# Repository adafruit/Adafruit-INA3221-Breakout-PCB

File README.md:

## Adafruit INA3221 - Triple 0-26 VDC, ±3.2 Amp Power Monitor - STEMMA QT / Qwiic PCB

<a href="http://www.adafruit.com/products/6062"><br/>
Click here to purchase one from the Adafruit shop</a>

PCB files for the Adafruit INA3221 - Triple 0-26 VDC, ±3.2 Amp Power Monitor - STEMMA QT / Qwiic. 

Format is EagleCAD schematic and board layout
* https://www.adafruit.com/product/6062

### Description

This breakout board will solve all your multi-rail power-monitoring problems. Instead of struggling with up to 6 multimeters, you can just use the handy INA3221 chip on this breakout to both measure both the high side voltage and DC current draw of up to three power supplies over I2C with ±1% precision.

Most current-measuring devices such as our current panel meter are only good for low side measuring. That means that unless you want to get a battery involved, you have to stick the measurement resistor between the target ground and true ground. This can cause problems with circuits since electronics tend to not like it when the ground references change and move with varying current draw. This chip is much smarter - it can handle high or low side current measuring, up to +26VDC, even though it is powered with 3 or 5V. It will also report back that high side voltage, which is great for tracking battery life or solar panels.

A precision amplifier measures the voltage across the built-in 0.05 ohm, 1% sense resistors. Since the amplifier maximum input difference is ±163.8mV this means it can measure up to ±3.2 Amps. With the internal 13 bit ADC, the resolution at ±3.2A range is 0.4mA. Advanced hackers can remove the 0.05 ohm current sense resistor and replace it with their own to change the range (say a 0.01 ohm to measure up 16.4 Amps with a resolution of 2mA)

Usage is simple. Power the sensor itself with 3 to 5VDC and connect the two I2C pins up to your microcontroller - the logic level will be the same as the Vin power level. Then connect your target power supplies to VIN1/2/3+ and the loads to ground to VIN1/2/3-. If you want, set up over-current alerts on the warning or critical IRQ pins. We have libraries in both Arduino and CircuitPython/Python so you can use it with boards as simple as Arduino-compatible ATmegas all the way up to the latest Raspberry Pi's.

You don't even need to solder the I2C and power lines: we pre-attach 3.5mm terminal blocks and added SparkFun qwiic compatible STEMMA QT connectors for the I2C bus. Just wire up to your favorite micro using a STEMMA QT adapter cable. The Stemma QT connectors also mean the INA3221 can be used with our various associated accessories. QT Cable is not included, but we have a variety in the shop. If you need access to all of the pins, we include 0.1" pin header (so you can easily attach this sensor to a breadboard).

### License

Adafruit invests time and resources providing this open source design, please support Adafruit and open-source hardware by purchasing products from [Adafruit](https://www.adafruit.com)!

Designed by Limor Fried/Ladyada for Adafruit Industries.

Creative Commons Attribution/Share-Alike, all text above must be included in any redistribution. 
See license.txt for additional details.

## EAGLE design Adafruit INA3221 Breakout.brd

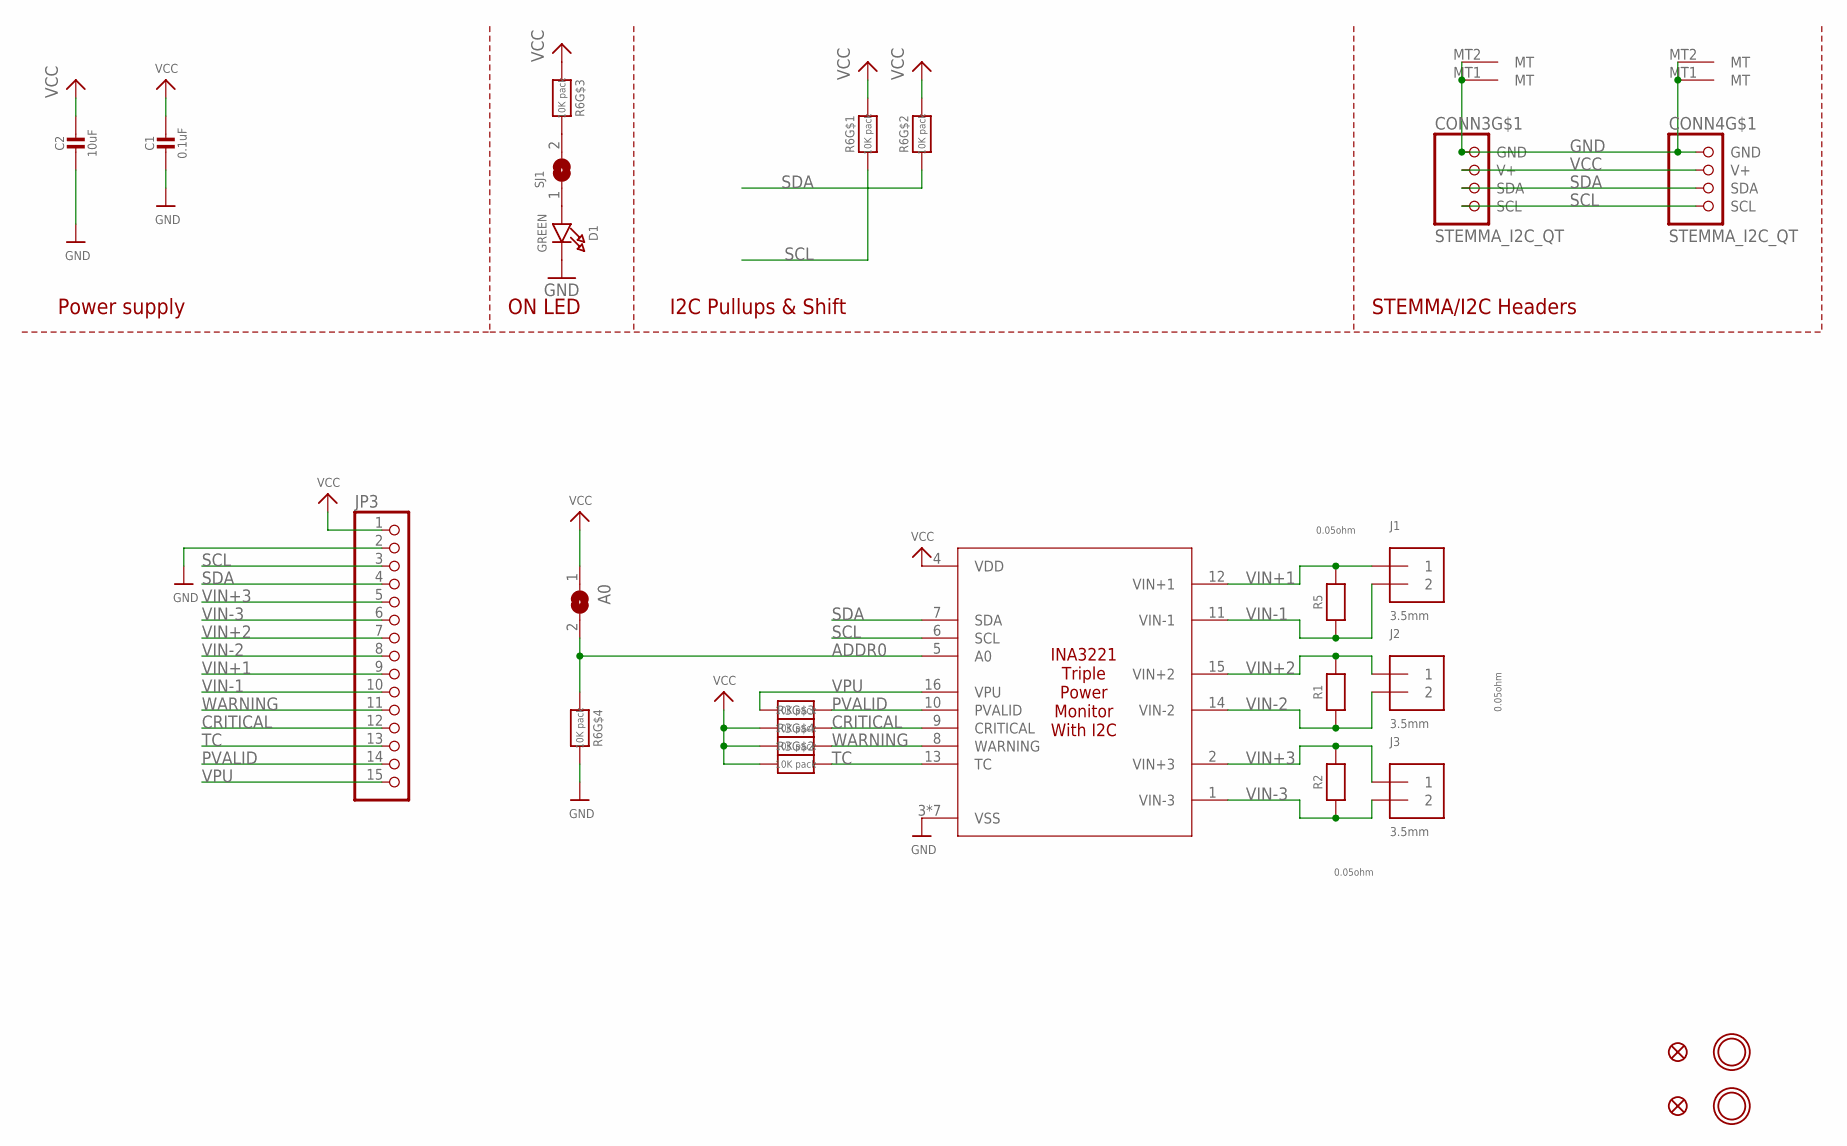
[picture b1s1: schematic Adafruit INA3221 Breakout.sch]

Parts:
A0: SOLDERJUMPERREFLOW_NOPASTE; SOLDERJUMPER_REFLOW_NOPASTE
C1: 0.1uF; 0603-NO
C2: 10uF; 0805-NO
CONN3, CONN4: STEMMA_I2C_QT; JST_SH4
D1: GREEN; CHIPLED_0603_NOOUTLINE
FID3, FID4: FIDUCIAL_1MM
IC1: INA3221; PVQFN-16
J1, J2, J3: 3.5mm; TERMBLOCK_1X2-3.5MM
JP3: HEADER-1X15; 1X15_ROUND_70
R1, R2, R5: 0.05ohm; _1206
R3, R6: 10K pack; RESPACK_4X0603
SJ1: SOLDERJUMPERCLOSED; SOLDERJUMPER_CLOSEDWIRE
U$20, U$21: MOUNTINGHOLE2.5; MOUNTINGHOLE_2.5_PLATED

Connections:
ADDR0: A0.2, IC1.5 (A0), R6.4 (1)
CRITICAL: IC1.9 (CRITICAL), JP3.12, R3.6 (2)
GND: C1.2, C2.2, CONN3.1 (GND), CONN3.MT1 (MT), CONN3.MT2 (MT), CONN4.1 (GND), CONN4.MT1 (MT), CONN4.MT2 (MT), D1.C, IC1.3 (VSS), IC1.P$18 (VSS), IC1.P$19 (VSS), IC1.P$20 (VSS), IC1.P$21 (VSS), IC1.P$22 (VSS), IC1.THERMAL (VSS), JP3.2, R6.5 (2)
unnamed: R6.6 (2), SJ1.2
unnamed: D1.A, SJ1.1
PVALID: IC1.10 (PVALID), JP3.14, R3.8 (2)
SCL: CONN3.4 (SCL), CONN4.4 (SCL), IC1.6 (SCL), JP3.3, R6.1
SDA: CONN3.3 (SDA), CONN4.3 (SDA), IC1.7 (SDA), JP3.4, R6.2 (1)
TC: IC1.13 (TC), JP3.13, R3.7 (2)
VCC: A0.1, C1.1, C2.1, CONN3.2 (V+), CONN4.2 (V+), IC1.4 (VDD), JP3.1, R3.2 (1), R3.3 (1), R3.4 (1), R6.3 (1), R6.7 (2), R6.8 (2)
VIN+1: IC1.12 (VIN+1), J1.1, JP3.9, R5.2
VIN+2: IC1.15 (VIN+2), J2.1, JP3.7, R1.2
VIN+3: IC1.2 (VIN+3), J3.1, JP3.5, R2.2
VIN-1: IC1.11 (VIN-1), J1.2, JP3.10, R5.1
VIN-2: IC1.14 (VIN-2), J2.2, JP3.8, R1.1
VIN-3: IC1.1 (VIN-3), J3.2, JP3.6, R2.1
VPU: IC1.16 (VPU), JP3.15, R3.1
WARNING: IC1.8 (WARNING), JP3.11, R3.5 (2)

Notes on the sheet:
I2C Pullups & Shift
STEMMA/I2C Headers
ON LED
Power supply

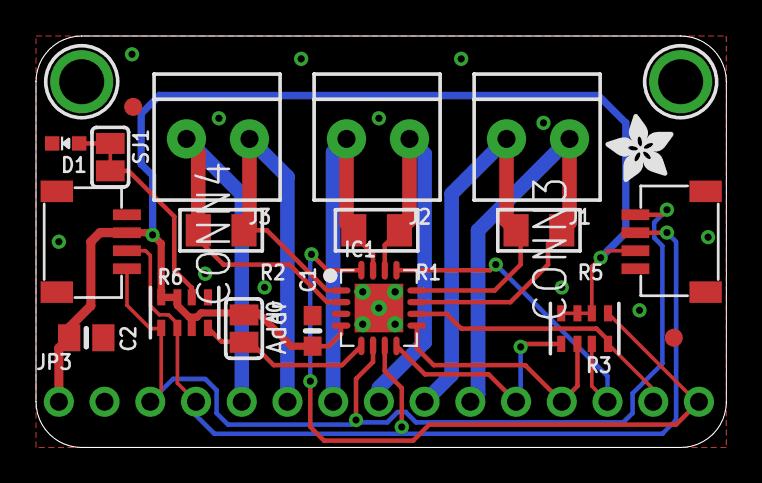
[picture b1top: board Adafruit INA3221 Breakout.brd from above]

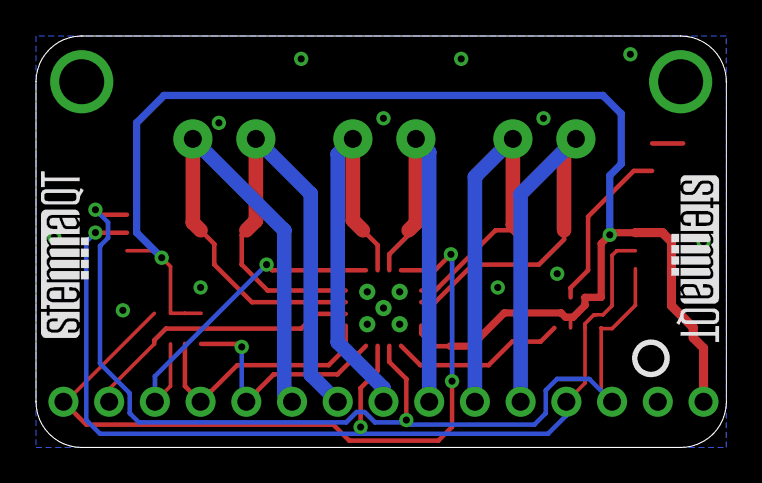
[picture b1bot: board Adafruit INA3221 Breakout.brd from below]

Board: 2 copper layers, 38.4 x 22.9 mm, 54 parts (7 on the bottom side), 18 nets.

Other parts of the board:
PLABEL0: PLABEL0
PLABEL1: PLABEL1
PLABEL2: PLABEL2
PLABEL3: PLABEL3
PLABEL4: PLABEL4
PLABEL5: PLABEL5
PLABEL6: PLABEL6
PLABEL7: PLABEL7
PLABEL8: PLABEL8
PLABEL9: PLABEL9
PLABEL10: PLABEL10
PLABEL11: PLABEL11
PLABEL12: PLABEL12
PLABEL13: PLABEL13
PLABEL14: PLABEL14
PLABEL15: PLABEL15
PLABEL16: PLABEL16
PLABEL17: PLABEL17
PLABEL18: PLABEL18
PLABEL19: PLABEL19
PLABEL20: PLABEL20
PLABEL21: PLABEL21
PLABEL22: PLABEL22
PLABEL23: PLABEL23
PLABEL24: PLABEL24
PLABEL25: PLABEL25
PLABEL26: PLABEL26
PLABEL27: PLABEL27
PLABEL28: PLABEL28
U$7: ADAFRUIT_3.5MM
U$30: PCBFEAT-REV-040
U$31, U$32: STEMMAQT

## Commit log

2024-10-17 cookiecutter
